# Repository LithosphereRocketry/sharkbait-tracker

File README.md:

# sharkbait-tracker
A small and low-cost GPS tracker for model rocketry applications.

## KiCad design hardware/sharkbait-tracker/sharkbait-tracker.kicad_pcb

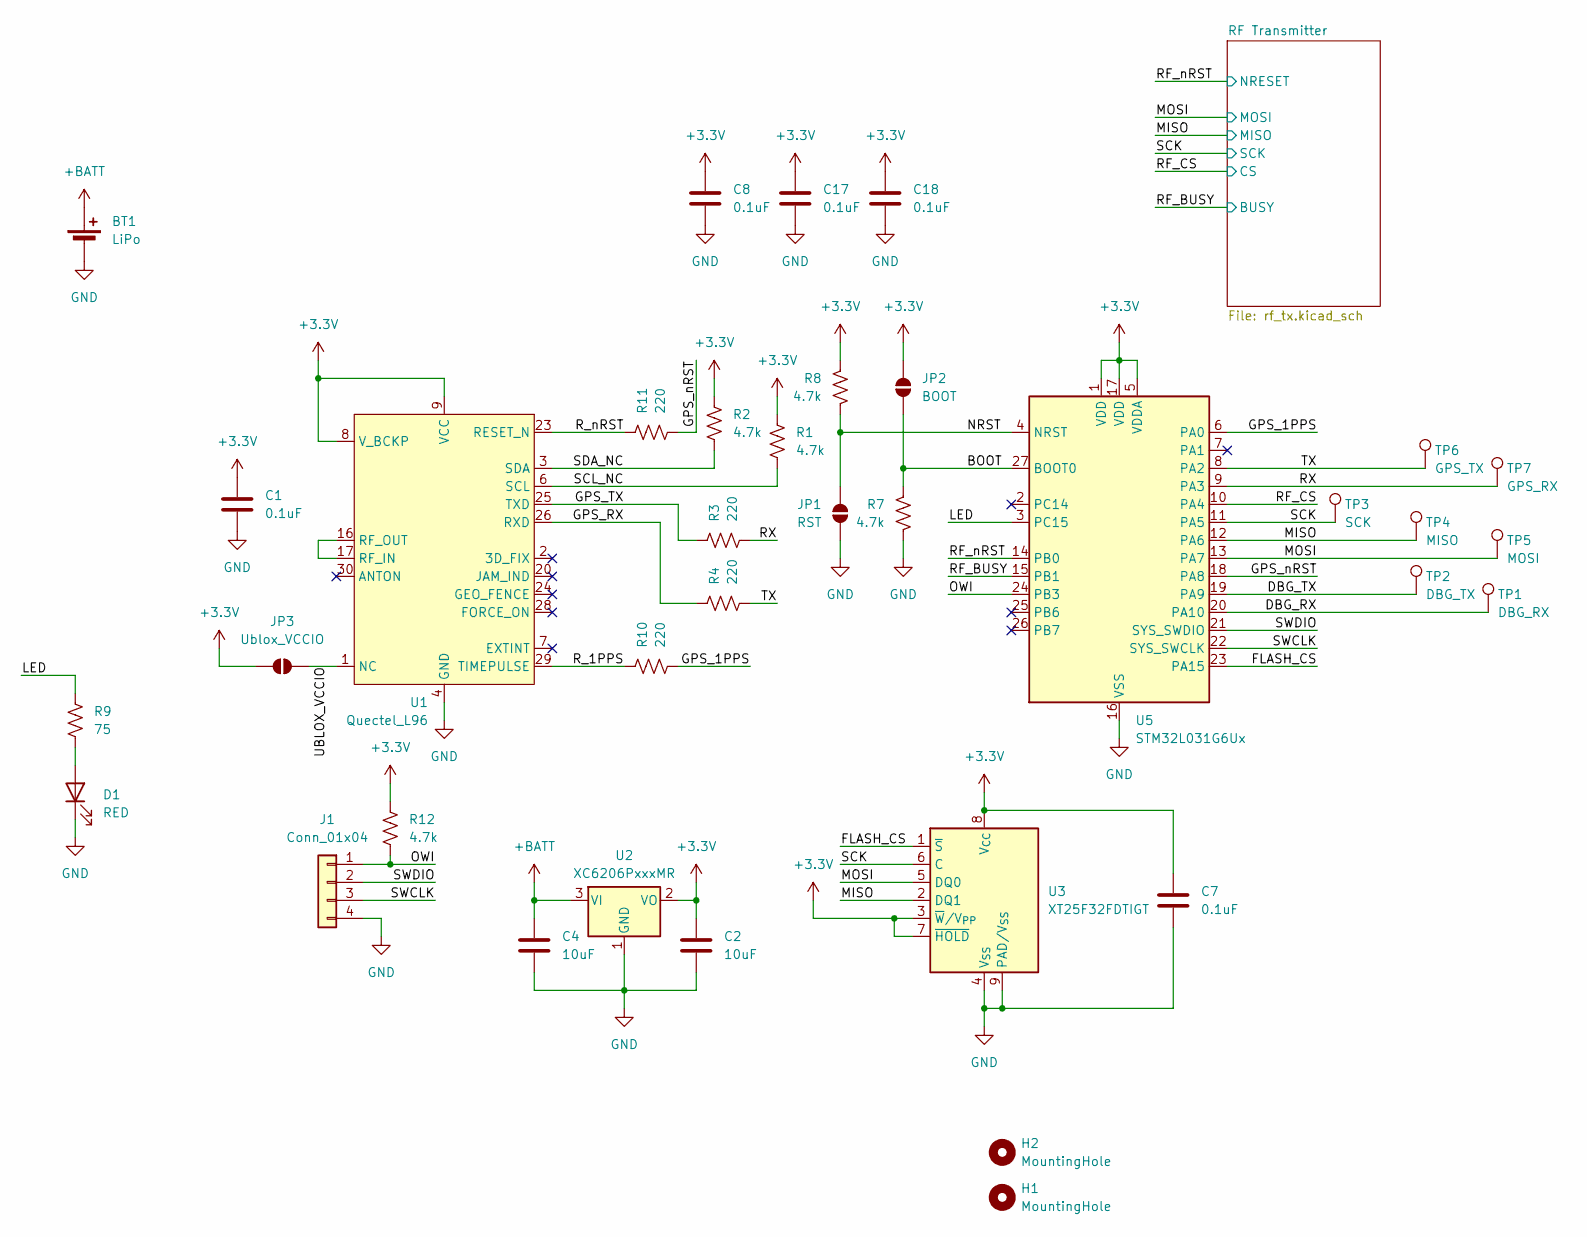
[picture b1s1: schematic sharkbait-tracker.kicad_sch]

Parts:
BT1: LiPo; PinHeader_1x02_P2.00mm_Vertical; JLCPCB_IGNORE ignore
C1, C7, C8, C17, C18: 0.1uF; C_0402_1005Metric; LCSC C1525
C2, C4: 10uF; C_0603_1608Metric; LCSC C19702
D1: RED; LED_0603_1608Metric; LCSC C2286
H1, H2: MountingHole; MountingHole_2.2mm_M2
J1: Conn_01x04; Molex_PicoBlade_53047-0410_1x04_P1.25mm_Vertical; JLCPCB_IGNORE ignore
JP1: RST; SolderJumper-2_P1.3mm_Open_RoundedPad1.0x1.5mm
JP2: BOOT; SolderJumper-2_P1.3mm_Open_RoundedPad1.0x1.5mm
JP3: Ublox_VCCIO; SolderJumper-2_P1.3mm_Open_TrianglePad1.0x1.5mm
R1, R2, R7, R8, R12: 4.7k; R_0402_1005Metric; LCSC C25900
R3, R4, R10, R11: 220; R_0402_1005Metric; LCSC C25091
R9: 75; R_0402_1005Metric; LCSC C25133
TP1: DBG_RX; TestPoint_Pad_D1.0mm
TP2: DBG_TX; TestPoint_Pad_D1.0mm
TP3: SCK; TestPoint_Pad_D1.0mm
TP4: MISO; TestPoint_Pad_D1.0mm
TP5: MOSI; TestPoint_Pad_D1.0mm
TP6: GPS_TX; TestPoint_Pad_D1.0mm
TP7: GPS_RX; TestPoint_Pad_D1.0mm
U1: Quectel_L96; CAM-M8_QuectelL96; LCSC C5197298
U2: XC6206PxxxMR; SOT-23-3; LCSC C5446
U3: XT25F32FDTIGT; Winbond_USON-8-1EP_3x2mm_P0.5mm_EP0.2x1.6mm; LCSC C7429719
U5: STM32L031G6Ux; QFN-28_4x4mm_P0.5mm; LCSC C96514

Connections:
+3.3V: C1.1, C2.1, C7.1, C8.1, C17.1, C18.1, JP2.2 (B), JP3.1 (A), R1.1, R2.1, R8.1, R12.1, U1.8 (V_BCKP), U1.9 (VCC), U2.2 (VO), U3.3 (~W/V_{PP}), U3.7 (~HOLD), U3.8 (V_{CC}), U5.1 (VDD), U5.5 (VDDA), U5.17 (VDD); also elsewhere on the board
+BATT: BT1.1 (+), C4.1, U2.3 (VI)
/BOOT: JP2.1 (A), R7.1, U5.27 (BOOT0)
/DBG_RX: TP1.1, U5.20 (PA10)
/DBG_TX: TP2.1, U5.19 (PA9)
/FLASH_CS: U3.1 (~S), U5.23 (PA15)
/GPS_1PPS: R10.2, U5.6 (PA0)
/GPS_RX: R4.1, U1.26 (RXD)
/GPS_TX: R3.1, U1.25 (TXD)
/GPS_nRST: R11.2, U5.18 (PA8)
/LED: R9.2, U5.3 (PC15)
/MISO: TP4.1, U3.2 (DQ1), U5.12 (PA6); also elsewhere on the board
/MOSI: TP5.1, U3.5 (DQ0), U5.13 (PA7); also elsewhere on the board
/NRST: JP1.2 (B), R8.2, U5.4 (NRST)
/OWI: J1.1, R12.2, U5.24 (PB3)
/RF_BUSY: U5.15 (PB1); also elsewhere on the board
/RF_CS: U5.10 (PA4); also elsewhere on the board
/RF_nRST: U5.14 (PB0); also elsewhere on the board
/RX: R3.2, TP7.1, U5.9 (PA3)
/R_1PPS: R10.1, U1.29 (TIMEPULSE)
/R_nRST: R11.1, U1.23 (RESET_N)
/SCK: TP3.1, U3.6 (C), U5.11 (PA5); also elsewhere on the board
/SCL_NC: R1.2, U1.6 (SCL)
/SDA_NC: R2.2, U1.3 (SDA)
/SWCLK: J1.3, U5.22 (SYS_SWCLK)
/SWDIO: J1.2, U5.21 (SYS_SWDIO)
/TX: R4.2, TP6.1, U5.8 (PA2)
/UBLOX_VCCIO: JP3.2 (B), U1.1 (NC)
GND: BT1.2 (-), C1.2, C2.2, C4.2, C7.2, C8.2, C17.2, C18.2, D1.1 (K), J1.4, JP1.1 (A), R7.2, U1.4 (GND), U1.5 (GND), U1.10 (GND), U1.11 (GND), U1.12 (GND), U1.13 (GND), U1.14 (GND), U1.15 (GND), U1.18 (GND), U1.19 (GND), U1.21 (GND), U1.22 (GND), U1.27 (GND), U1.31 (GND), U2.1 (GND), U3.4 (V_{SS}), U3.9 (PAD/V_{SS}), U5.16 (VSS), U5.28 (VSS); also elsewhere on the board
unnamed: D1.2 (A), R9.1
unnamed: U1.16 (RF_OUT), U1.17 (RF_IN)

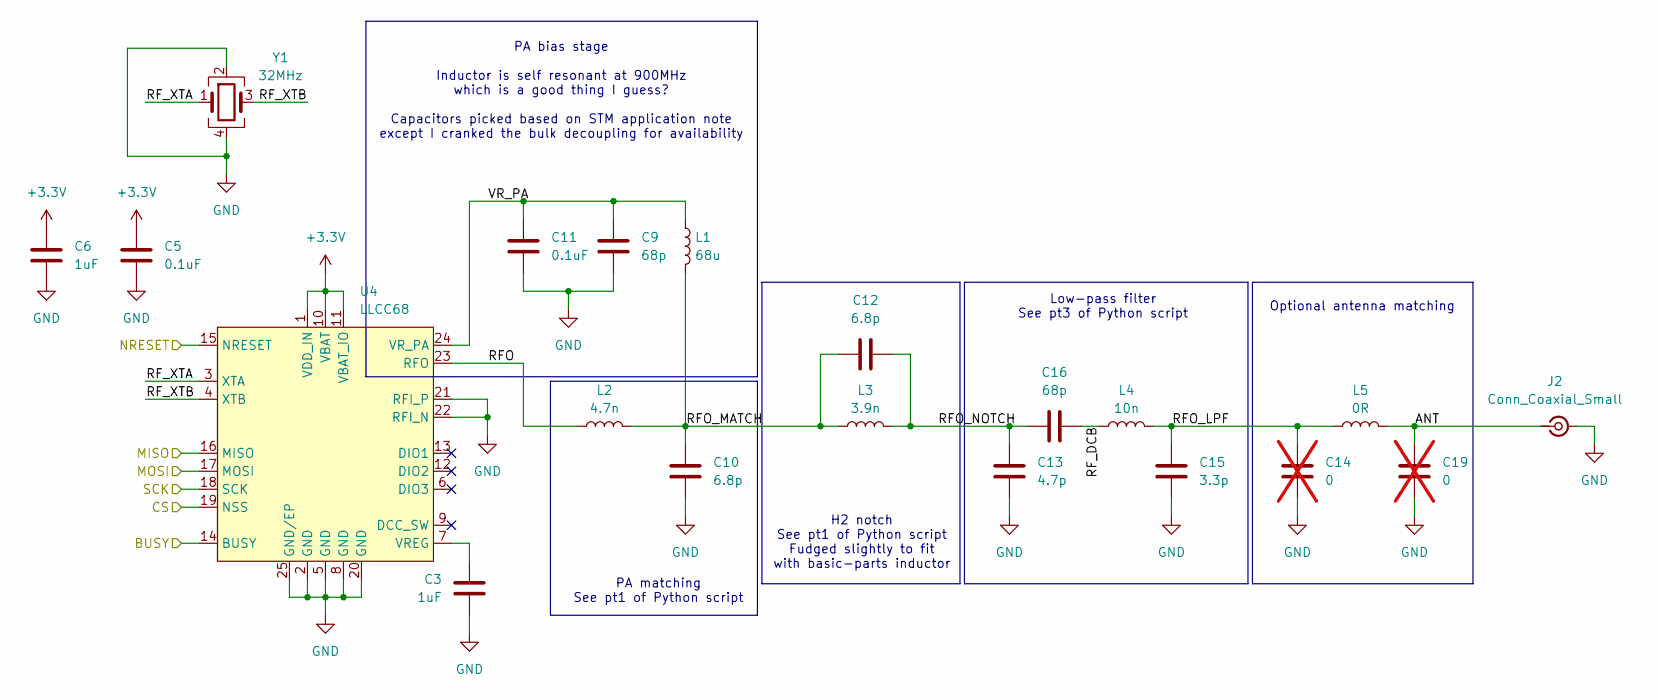
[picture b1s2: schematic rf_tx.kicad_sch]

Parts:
C3, C6: 1uF; C_0402_1005Metric; LCSC C52923
C5, C11: 0.1uF; C_0402_1005Metric; LCSC C1525
C9, C16: 68p; C_0402_1005Metric; LCSC C14441
C10, C12: 6.8p; C_0402_1005Metric; LCSC C1576
C13: 4.7p; C_0402_1005Metric; LCSC C1569
C14, C19: 0; C_0402_1005Metric; LCSC C1565; not fitted
C15: 3.3p; C_0402_1005Metric; LCSC C1565
J2: Conn_Coaxial_Small; SMA_Samtec_SMA-J-P-H-ST-EM1_EdgeMount_WireWhip; JLCPCB_IGNORE ignore
L1: 68u; L_0603_1608Metric; LCSC C13415
L2: 4.7n; L_0402_1005Metric; LCSC C13595
L3: 3.9n; L_0402_1005Metric; LCSC C14033
L4: 10n; L_0402_1005Metric; LCSC C27147
L5: 0R; L_0402_1005Metric; LCSC C17168
U4: LLCC68; QFN-24-1EP_4x4mm_P0.5mm_EP2.7x2.7mm_ThermalVias; LCSC C5120261
Y1: 32MHz; Crystal_SMD_2016-4Pin_2.0x1.6mm; LCSC C843260

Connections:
+3.3V: C5.1, C6.1, U4.1 (VDD_IN), U4.10 (VBAT), U4.11 (VBAT_IO); also elsewhere on the board
/MISO: U4.16 (MISO); also elsewhere on the board
/MOSI: U4.17 (MOSI); also elsewhere on the board
/RF Transmitter/ANT: C19.1, J2.1 (In), L5.2
/RF Transmitter/RFO: L2.1, U4.23 (RFO)
/RF Transmitter/RFO_LPF: C14.1, C15.1, L4.2, L5.1
/RF Transmitter/RFO_MATCH: C10.1, C12.1, L1.2, L2.2, L3.1
/RF Transmitter/RFO_NOTCH: C12.2, C13.1, C16.1, L3.2
/RF Transmitter/RF_DCB: C16.2, L4.1
/RF Transmitter/RF_XTA: U4.3 (XTA), Y1.1
/RF Transmitter/RF_XTB: U4.4 (XTB), Y1.3
/RF Transmitter/VR_PA: C9.1, C11.1, L1.1, U4.24 (VR_PA)
/RF_BUSY: U4.14 (BUSY); also elsewhere on the board
/RF_CS: U4.19 (NSS); also elsewhere on the board
/RF_nRST: U4.15 (NRESET); also elsewhere on the board
/SCK: U4.18 (SCK); also elsewhere on the board
GND: C3.2, C5.2, C6.2, C9.2, C10.2, C11.2, C13.2, C14.2, C15.2, C19.2, J2.2 (Ext), U4.2 (GND), U4.5 (GND), U4.8 (GND), U4.20 (GND), U4.21 (RFI_P), U4.22 (RFI_N), U4.25 (GND/EP), Y1.2, Y1.4; also elsewhere on the board
unnamed: C3.1, U4.7 (VREG)

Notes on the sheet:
PA bias stage Inductor is self resonant at 900MHz which is a good thing I guess? Capacitors picked based on STM application note except I cranked the bulk decoupling for availability
Optional antenna matching
Low-pass filter See pt3 of Python script
PA matching See pt1 of Python script
H2 notch See pt1 of Python script Fudged slightly to fit with basic-parts inductor

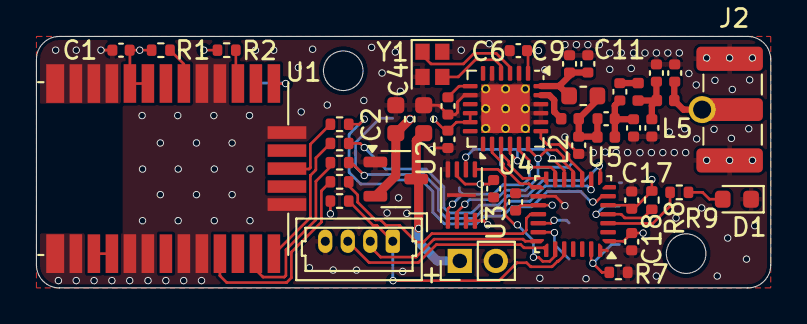
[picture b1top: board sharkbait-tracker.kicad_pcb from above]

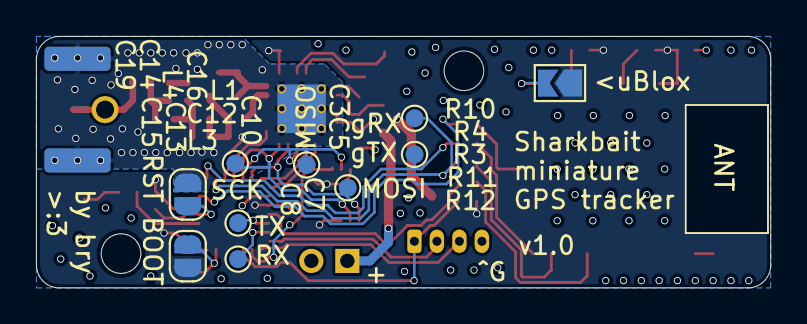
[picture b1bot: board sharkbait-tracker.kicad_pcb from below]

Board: 4 copper layers, 40.8 x 14.0 mm, 56 parts (10 on the bottom side), 41 nets.

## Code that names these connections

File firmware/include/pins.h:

#ifndef PINS_H
#define PINS_H

#include <Arduino.h>

static const uint8_t P_TX = PA2, P_RX = PA3, P_DBG_TX = PA9, P_DBG_RX = PA10;
static const uint8_t P_MISO = PA6, P_MOSI = PA7, P_SCK = PA5;
static const uint8_t P_RF_CS = PA4, P_RF_nRST = PB0, P_RF_BUSY = PB1;
static const uint8_t P_GPS_1PPS = PA0, P_GPS_nRST = PA8;
static const uint8_t P_FLASH_CS = PA15;
static const uint8_t P_OWI = PB3, P_LED = PC15;

#endif

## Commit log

2025-01-17 Losing my soul to dark RF magic
2025-01-21 Most of the layout done, but might break things
2025-01-21 Everything fits, might rearrange a little
2025-01-22 Removed battery voltage divider again, and rounded corners
2025-01-23 Combination antenna footprint and build automation
2025-01-26 Widened RF PA traces a smidge
2025-06-09 Updated vias for easier tolerances
2025-06-09 basic low-smarts firmware, enough to work
2025-06-09 Narrowed pads to match ublox footprint (the quectel one is extra wide for some reason
